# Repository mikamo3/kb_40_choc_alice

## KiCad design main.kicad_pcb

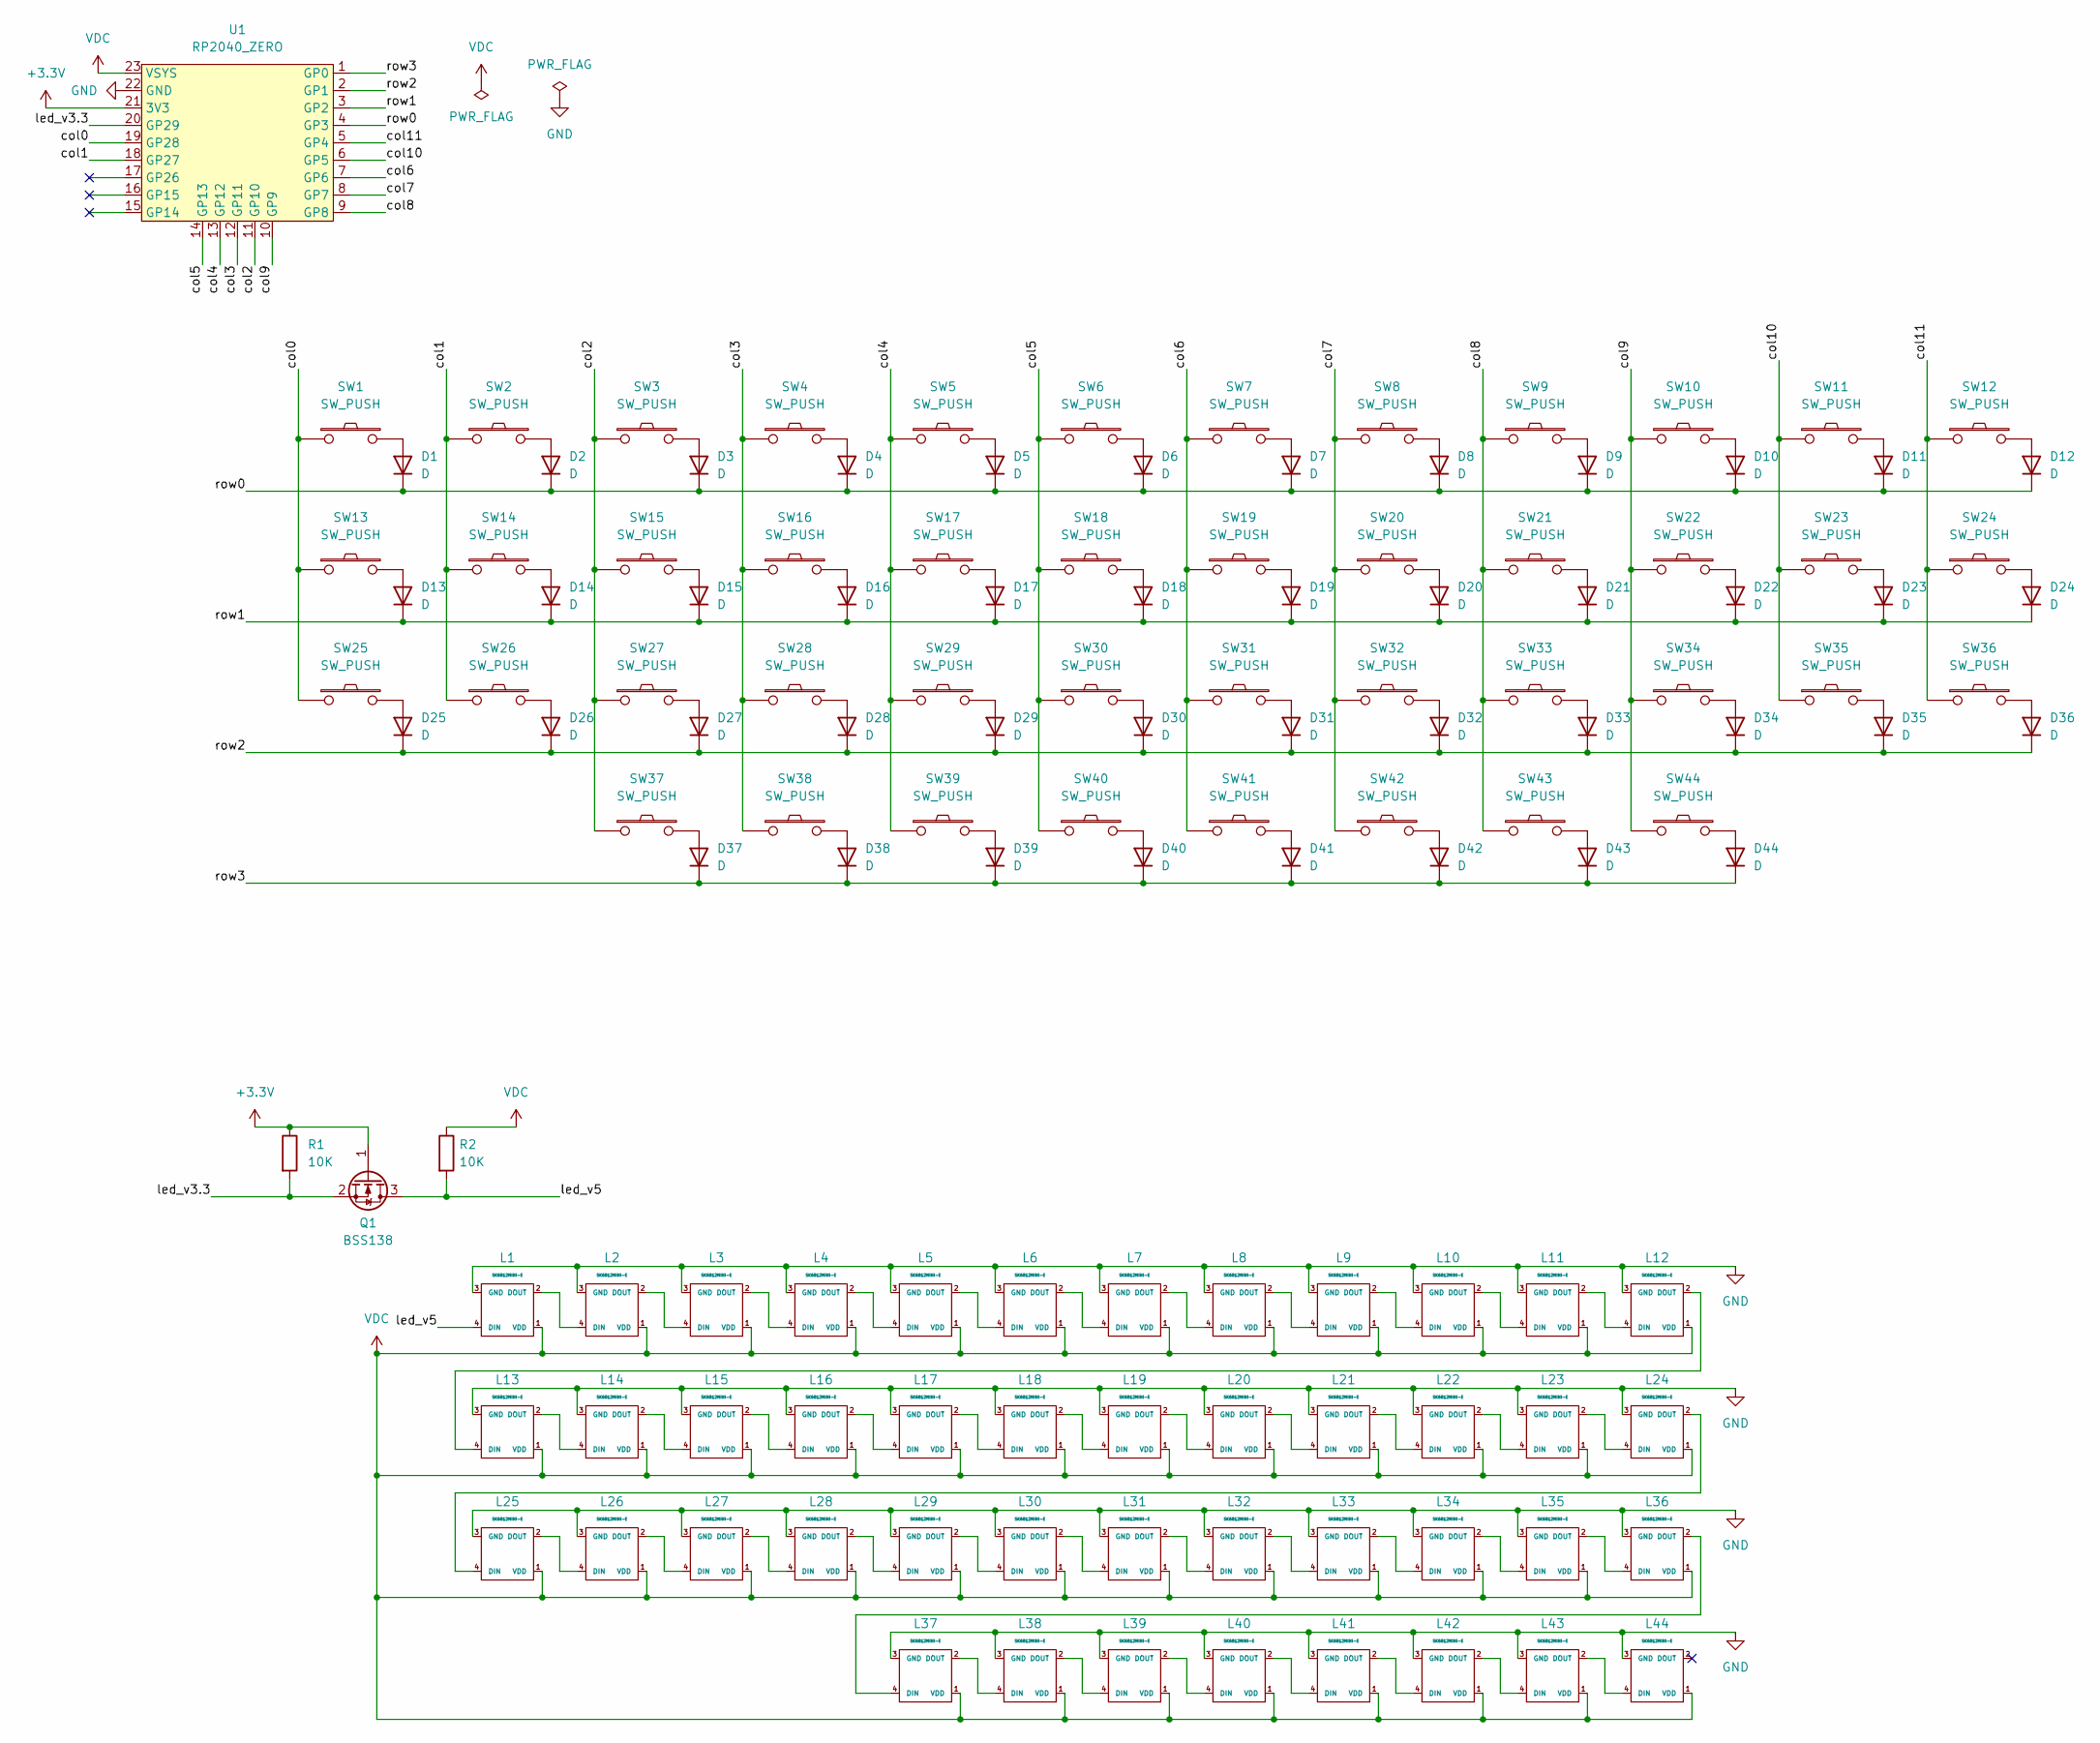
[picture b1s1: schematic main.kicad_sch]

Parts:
D1, D2, D3, D4, D5, D6, D7, D8, D9, D10, D11, D12, D13, D14, D15, D16, D17, D18, D19, D20, D21, D22, D23, D24, D25, D26, D27, D28, D29, D30, D31, D32, D33, D34, D35, D36, D37, D38, D39, D40, D41, D42, D43, D44: D; Diode_SOD123
L1, L2, L3, L4, L5, L6, L7, L8, L9, L10, L11, L12, L13, L14, L15, L16, L17, L18, L19, L20, L21, L22, L23, L24, L25, L26, L27, L28, L29, L30, L31, L32, L33, L34, L35, L36, L37, L38, L39, L40, L41, L42, L43, L44: SK6812MINI-E; YS-SK6812MINI-E
Q1: BSS138; SOT-23
R1, R2: 10K; R_1206_3216Metric_Pad1.30x1.75mm_HandSolder
SW1, SW2, SW3, SW4, SW5, SW6, SW7, SW8, SW9, SW10, SW11, SW12, SW13, SW14, SW15, SW16, SW17, SW18, SW19, SW20, SW21, SW22, SW23, SW24, SW25, SW26, SW27, SW28, SW29, SW30, SW31, SW32, SW33, SW34, SW35, SW36, SW37, SW38, SW39, SW40, SW41, SW42, SW43, SW44: SW_PUSH; SW_ChocV1_Hotswap_1.0u
U1: RP2040_ZERO; RP2040-ZERO_SMD

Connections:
+3.3V: Q1.1 (G), R1.1, U1.21 (3V3)
/col0: SW1.1, SW13.1, SW25.1, U1.19 (GP28)
/col1: SW2.1, SW14.1, SW26.1, U1.18 (GP27)
/col2: SW3.1, SW15.1, SW27.1, SW37.1, U1.11 (GP10)
/col3: SW4.1, SW16.1, SW28.1, SW38.1, U1.12 (GP11)
/col4: SW5.1, SW17.1, SW29.1, SW39.1, U1.13 (GP12)
/col5: SW6.1, SW18.1, SW30.1, SW40.1, U1.14 (GP13)
/col6: SW7.1, SW19.1, SW31.1, SW41.1, U1.7 (GP6)
/col7: SW8.1, SW20.1, SW32.1, SW42.1, U1.8 (GP7)
/col8: SW9.1, SW21.1, SW33.1, SW43.1, U1.9 (GP8)
/col9: SW10.1, SW22.1, SW34.1, SW44.1, U1.10 (GP9)
/col10: SW11.1, SW23.1, SW35.1, U1.6 (GP5)
/col11: SW12.1, SW24.1, SW36.1, U1.5 (GP4)
/led_v3.3: Q1.2 (S), R1.2, U1.20 (GP29)
/led_v5: L1.4 (DIN), Q1.3 (D), R2.2
/row0: D1.1 (K), D2.1 (K), D3.1 (K), D4.1 (K), D5.1 (K), D6.1 (K), D7.1 (K), D8.1 (K), D9.1 (K), D10.1 (K), D11.1 (K), D12.1 (K), U1.4 (GP3)
/row1: D13.1 (K), D14.1 (K), D15.1 (K), D16.1 (K), D17.1 (K), D18.1 (K), D19.1 (K), D20.1 (K), D21.1 (K), D22.1 (K), D23.1 (K), D24.1 (K), U1.3 (GP2)
/row2: D25.1 (K), D26.1 (K), D27.1 (K), D28.1 (K), D29.1 (K), D30.1 (K), D31.1 (K), D32.1 (K), D33.1 (K), D34.1 (K), D35.1 (K), D36.1 (K), U1.2 (GP1)
/row3: D37.1 (K), D38.1 (K), D39.1 (K), D40.1 (K), D41.1 (K), D42.1 (K), D43.1 (K), D44.1 (K), U1.1 (GP0)
GND: L1.3 (GND), L2.3 (GND), L3.3 (GND), L4.3 (GND), L5.3 (GND), L6.3 (GND), L7.3 (GND), L8.3 (GND), L9.3 (GND), L10.3 (GND), L11.3 (GND), L12.3 (GND), L13.3 (GND), L14.3 (GND), L15.3 (GND), L16.3 (GND), L17.3 (GND), L18.3 (GND), L19.3 (GND), L20.3 (GND), L21.3 (GND), L22.3 (GND), L23.3 (GND), L24.3 (GND), L25.3 (GND), L26.3 (GND), L27.3 (GND), L28.3 (GND), L29.3 (GND), L30.3 (GND), L31.3 (GND), L32.3 (GND), L33.3 (GND), L34.3 (GND), L35.3 (GND), L36.3 (GND), L37.3 (GND), L38.3 (GND), L39.3 (GND), L40.3 (GND), L41.3 (GND), L42.3 (GND), L43.3 (GND), L44.3 (GND), U1.22 (GND)
unnamed: D1.2 (A), SW1.2
unnamed: D2.2 (A), SW2.2
unnamed: D3.2 (A), SW3.2
unnamed: D4.2 (A), SW4.2
unnamed: D5.2 (A), SW5.2
unnamed: D6.2 (A), SW6.2
unnamed: D7.2 (A), SW7.2
unnamed: D8.2 (A), SW8.2
unnamed: D9.2 (A), SW9.2
unnamed: D10.2 (A), SW10.2
unnamed: D11.2 (A), SW11.2
unnamed: D12.2 (A), SW12.2
unnamed: D13.2 (A), SW13.2
unnamed: D14.2 (A), SW14.2
unnamed: D15.2 (A), SW15.2
unnamed: D16.2 (A), SW16.2
unnamed: D17.2 (A), SW17.2
unnamed: D18.2 (A), SW18.2
unnamed: D19.2 (A), SW19.2
unnamed: D20.2 (A), SW20.2
unnamed: D21.2 (A), SW21.2
unnamed: D22.2 (A), SW22.2
unnamed: D23.2 (A), SW23.2
unnamed: D24.2 (A), SW24.2
unnamed: D25.2 (A), SW25.2
unnamed: D26.2 (A), SW26.2
unnamed: D27.2 (A), SW27.2
unnamed: D28.2 (A), SW28.2
unnamed: D29.2 (A), SW29.2
unnamed: D30.2 (A), SW30.2
unnamed: D31.2 (A), SW31.2
unnamed: D32.2 (A), SW32.2
unnamed: D33.2 (A), SW33.2
unnamed: D34.2 (A), SW34.2
unnamed: D35.2 (A), SW35.2
unnamed: D36.2 (A), SW36.2
unnamed: D37.2 (A), SW37.2
unnamed: D38.2 (A), SW38.2
unnamed: D39.2 (A), SW39.2
unnamed: D40.2 (A), SW40.2
unnamed: D41.2 (A), SW41.2
unnamed: D42.2 (A), SW42.2
unnamed: D43.2 (A), SW43.2
unnamed: D44.2 (A), SW44.2
unnamed: L1.2 (DOUT), L2.4 (DIN)
unnamed: L2.2 (DOUT), L3.4 (DIN)
unnamed: L3.2 (DOUT), L4.4 (DIN)
unnamed: L4.2 (DOUT), L5.4 (DIN)
unnamed: L5.2 (DOUT), L6.4 (DIN)
unnamed: L6.2 (DOUT), L7.4 (DIN)
unnamed: L7.2 (DOUT), L8.4 (DIN)
unnamed: L8.2 (DOUT), L9.4 (DIN)
unnamed: L9.2 (DOUT), L10.4 (DIN)
unnamed: L10.2 (DOUT), L11.4 (DIN)
unnamed: L11.2 (DOUT), L12.4 (DIN)
unnamed: L12.2 (DOUT), L13.4 (DIN)
unnamed: L13.2 (DOUT), L14.4 (DIN)
unnamed: L14.2 (DOUT), L15.4 (DIN)
unnamed: L15.2 (DOUT), L16.4 (DIN)
unnamed: L16.2 (DOUT), L17.4 (DIN)
unnamed: L17.2 (DOUT), L18.4 (DIN)
unnamed: L18.2 (DOUT), L19.4 (DIN)
unnamed: L19.2 (DOUT), L20.4 (DIN)
unnamed: L20.2 (DOUT), L21.4 (DIN)
unnamed: L21.2 (DOUT), L22.4 (DIN)
unnamed: L22.2 (DOUT), L23.4 (DIN)
unnamed: L23.2 (DOUT), L24.4 (DIN)
unnamed: L24.2 (DOUT), L25.4 (DIN)
unnamed: L25.2 (DOUT), L26.4 (DIN)
unnamed: L26.2 (DOUT), L27.4 (DIN)
unnamed: L27.2 (DOUT), L28.4 (DIN)
unnamed: L28.2 (DOUT), L29.4 (DIN)
unnamed: L29.2 (DOUT), L30.4 (DIN)
unnamed: L30.2 (DOUT), L31.4 (DIN)
unnamed: L31.2 (DOUT), L32.4 (DIN)
unnamed: L32.2 (DOUT), L33.4 (DIN)
unnamed: L33.2 (DOUT), L34.4 (DIN)
unnamed: L34.2 (DOUT), L35.4 (DIN)
unnamed: L35.2 (DOUT), L36.4 (DIN)
unnamed: L36.2 (DOUT), L37.4 (DIN)
unnamed: L37.2 (DOUT), L38.4 (DIN)
unnamed: L38.2 (DOUT), L39.4 (DIN)
unnamed: L39.2 (DOUT), L40.4 (DIN)
unnamed: L40.2 (DOUT), L41.4 (DIN)
unnamed: L41.2 (DOUT), L42.4 (DIN)
unnamed: L42.2 (DOUT), L43.4 (DIN)
unnamed: L43.2 (DOUT), L44.4 (DIN)
VDC: L1.1 (VDD), L2.1 (VDD), L3.1 (VDD), L4.1 (VDD), L5.1 (VDD), L6.1 (VDD), L7.1 (VDD), L8.1 (VDD), L9.1 (VDD), L10.1 (VDD), L11.1 (VDD), L12.1 (VDD), L13.1 (VDD), L14.1 (VDD), L15.1 (VDD), L16.1 (VDD), L17.1 (VDD), L18.1 (VDD), L19.1 (VDD), L20.1 (VDD), L21.1 (VDD), L22.1 (VDD), L23.1 (VDD), L24.1 (VDD), L25.1 (VDD), L26.1 (VDD), L27.1 (VDD), L28.1 (VDD), L29.1 (VDD), L30.1 (VDD), L31.1 (VDD), L32.1 (VDD), L33.1 (VDD), L34.1 (VDD), L35.1 (VDD), L36.1 (VDD), L37.1 (VDD), L38.1 (VDD), L39.1 (VDD), L40.1 (VDD), L41.1 (VDD), L42.1 (VDD), L43.1 (VDD), L44.1 (VDD), R2.1, U1.23 (VSYS)

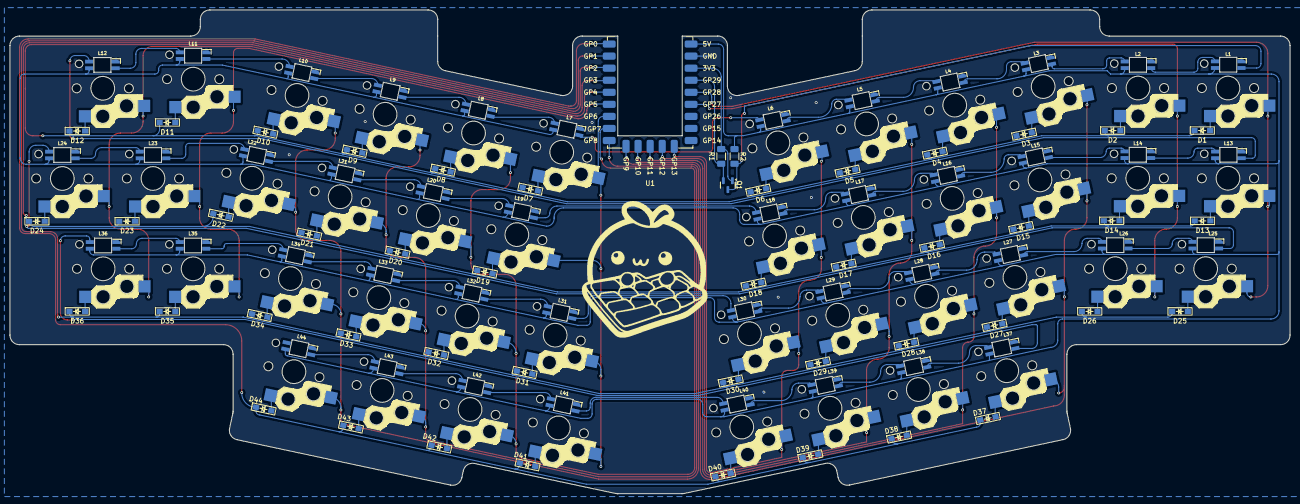
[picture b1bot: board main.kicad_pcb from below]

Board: 2 copper layers, 269.7 x 101.9 mm, 136 parts (92 on the bottom side), 108 nets.

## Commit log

2024-09-14 :sparkles: (layout) add
2024-09-23 Add .gitignore and .gitmodules for KiCad project
2024-09-23 Add KiCad symbol and footprint libraries
2024-09-23 Add MIT License
2024-10-04 :sparkles: (v1) Done. Pre-Order Final Review
2024-11-06 :sparkles: (layout) Fix legend
2024-11-17 :sparkles: (fix)
